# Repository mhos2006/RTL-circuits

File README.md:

# Resistor-Transistor Logic (RTL) Combinational Circuits

This repository documents the design, assembly, and testing of fundamental logic gates using discrete Bipolar Junction Transistors (BJTs) and passive components.

### Hardware and Components
*   **Transistors:** 2N3904 NPN Bipolar Junction Transistors
*   **Passives:** Assorted through-hole resistors for base biasing and load management
*   **Platform:** 830-point solderless breadboard
*   **Power:** 5V regulated DC supply

### Completed Logic Gates

#### 1. NOT Gate (Inverter)
*   **Status:** Completed
*   **Description:** Built using a single NPN transistor. The circuit successfully inverts the input signal, driving the output low when the input is driven high, and allowing the output to float high when the input is low.

#### 2. NAND Gate
*   **Status:** Completed
*   **Description:** Constructed with two BJTs in a series configuration. The output is pulled to ground only when both inputs are actively driven high.

#### 3. NOR Gate
*   **Status:** Completed
*   **Description:** Implemented using two BJTs in a parallel configuration. If either input receives a high signal, the output is pulled low. 
*   **Note:** Physical assembly and testing were successfully verified on the breadboard. While photographic documentation of the physical build is not included, the provided KiCad schematics serve as the primary technical reference for the design and routing.

### Planned Circuits
*   **AND Gate**
*   **OR Gate**
*   **XOR Gate**

### Documentation
In each gate file, I have included the schematic in KiCad and a PDF of it too. The PCB files are also they but are incomplete.

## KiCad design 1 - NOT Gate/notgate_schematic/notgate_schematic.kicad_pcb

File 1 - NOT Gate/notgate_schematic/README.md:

# NOT Gate

## Overview

Building an invertor (NOT) circuit using resistors and transistors.

## Hardware Specifications

- **Collector Resistor:** 1kΩ
- **Base Resistor:** 10kΩ
- **Brain:** 2N3904 BJT Transistor
- **Circuit tester:** LED

## Prerequisites
To achieve my 5V power rail, I used a battery pack regulated to output 5V. Here is a link to the repository:
[5V Linear Breadboard Power Supply](https://github.com/mhos2006/starter-dc-makeshift-power-supply) 

## Schematic

## Testing

In this clip, I initially have the input wire connected to GND. The LED will remain lit up until the wire is connected to the 5V rail, where the signal is inverted and the transistor is on.

https://github.com/user-attachments/assets/247801db-2280-493d-9bdd-d6d0273200bf

## Schematic and PCB Documentation

I created the schematic using KiCad software. While my schematic has been verified, I have not yet moved the components over to PCB software as I must still add component footnotes. PCB layout and component placement is in progress.

## Documentation

For a full breakdown of the empirical voltage measurements and analysis, please see the attached technical report .docx.

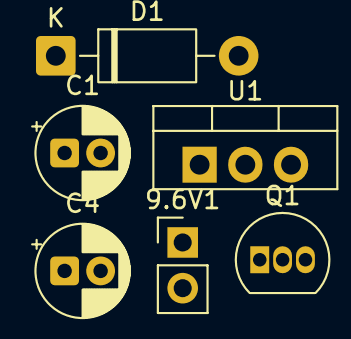
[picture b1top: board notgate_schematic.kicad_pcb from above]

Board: 2 copper layers, 6 parts (0 on the bottom side), 4 nets, no tracks yet.

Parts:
9.6V1: Battery; PinHeader_1x02_P2.54mm_Vertical
C1: C_Polarized 100μF; CP_Radial_D5.0mm_P2.00mm
C4: C_Polarized 10μF; CP_Radial_D5.0mm_P2.00mm
D1: 1N4007; D_DO-41_SOD81_P10.16mm_Horizontal
Q1: 2N3904; TO-92_Inline
U1: L7805; TO-220-3_Vertical

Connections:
+5V: C4.1, U1.3 (OUT)
GND: 9.6V1.2 (-), C1.2, C4.2, Q1.1 (E), U1.2 (GND)
unnamed: 9.6V1.1 (+), D1.2 (A)
unnamed: C1.1, D1.1 (K), U1.1 (IN)
